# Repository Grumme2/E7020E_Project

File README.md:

# E7020E_Project

## Project Description

Our project purpose is to see whether a person is inside a perimeter or not. If the person is outside, a lamp on the board will light up.
This is going to be done with a MURATA board and a gps. We also have to implement a way to see the battery level. With the LoRa we are going to transmit the battery level, and if a user exits the perimeter, we are sending that users location.

## Higher grade

The group is aming for a higher grade than a basic pass. We are going to try to implement a charger of Lipo batteries, so that a user can charge a battery. 

## Components
* GPS: 410-237 - PmodGPS, Module UART, Digilent
* Battery charger: MCP73831T-2ACI/OT
* Battery: PIS-1218 - PiJuice Zero LiPo Battery, 500mAh, Pi Supply

https://docs.google.com/document/d/1sqJ3TY8bH1azIesI4otk2LLjVwCMFet3OU3TrjOT8jw/edit?usp=sharing

## Setup/Starting the project

### Prerequisites

In order to have the project working as intended you need to have the following things installed: 

* rustup 
* llvm-8.0
* llvm-config
* openocd
* gcc
* arm-none-eabi-gcc

### Building/running the project

First install rustup by following the instructions on https://rustup.rs/
After the installation you need to switch to the nightly toolchain rustup can use. First list the versions that are available:

`rustup toolchain list`

Then set the nightly toolchain as default:

`rustup default <nightly-toolchain>`

Then you need to install the following dependencies using rustup:

`rustup target add thumbv6m-none-eabi`

In order to start the project you first have to redirect to the **project_code** folder.

 `cd project_code`

 From that you need to make sure that you have a file called **stm32l0_dual_bank.cfg** in the **target** folder. If not, create a new file with that name that contains everything from https://github.com/ntfreak/openocd/blob/master/tcl/target/stm32l0_dual_bank.cfg

After this you may finally start **openocd**:

`openocd -f openocd.cfg`

Then open a new terminal window and redirect to the **project_code** directory, and from that you may run the program: 

`cargo run`

Now you should have a fully functional GPS-tracker on your hands!

## Team
* Anton Grahn - antgra-6@student.ltu.se
* Tom Hammarkvist - tomham-3@student.ltu.se
* Rickard Holmberg - richol-6@student.ltu.se

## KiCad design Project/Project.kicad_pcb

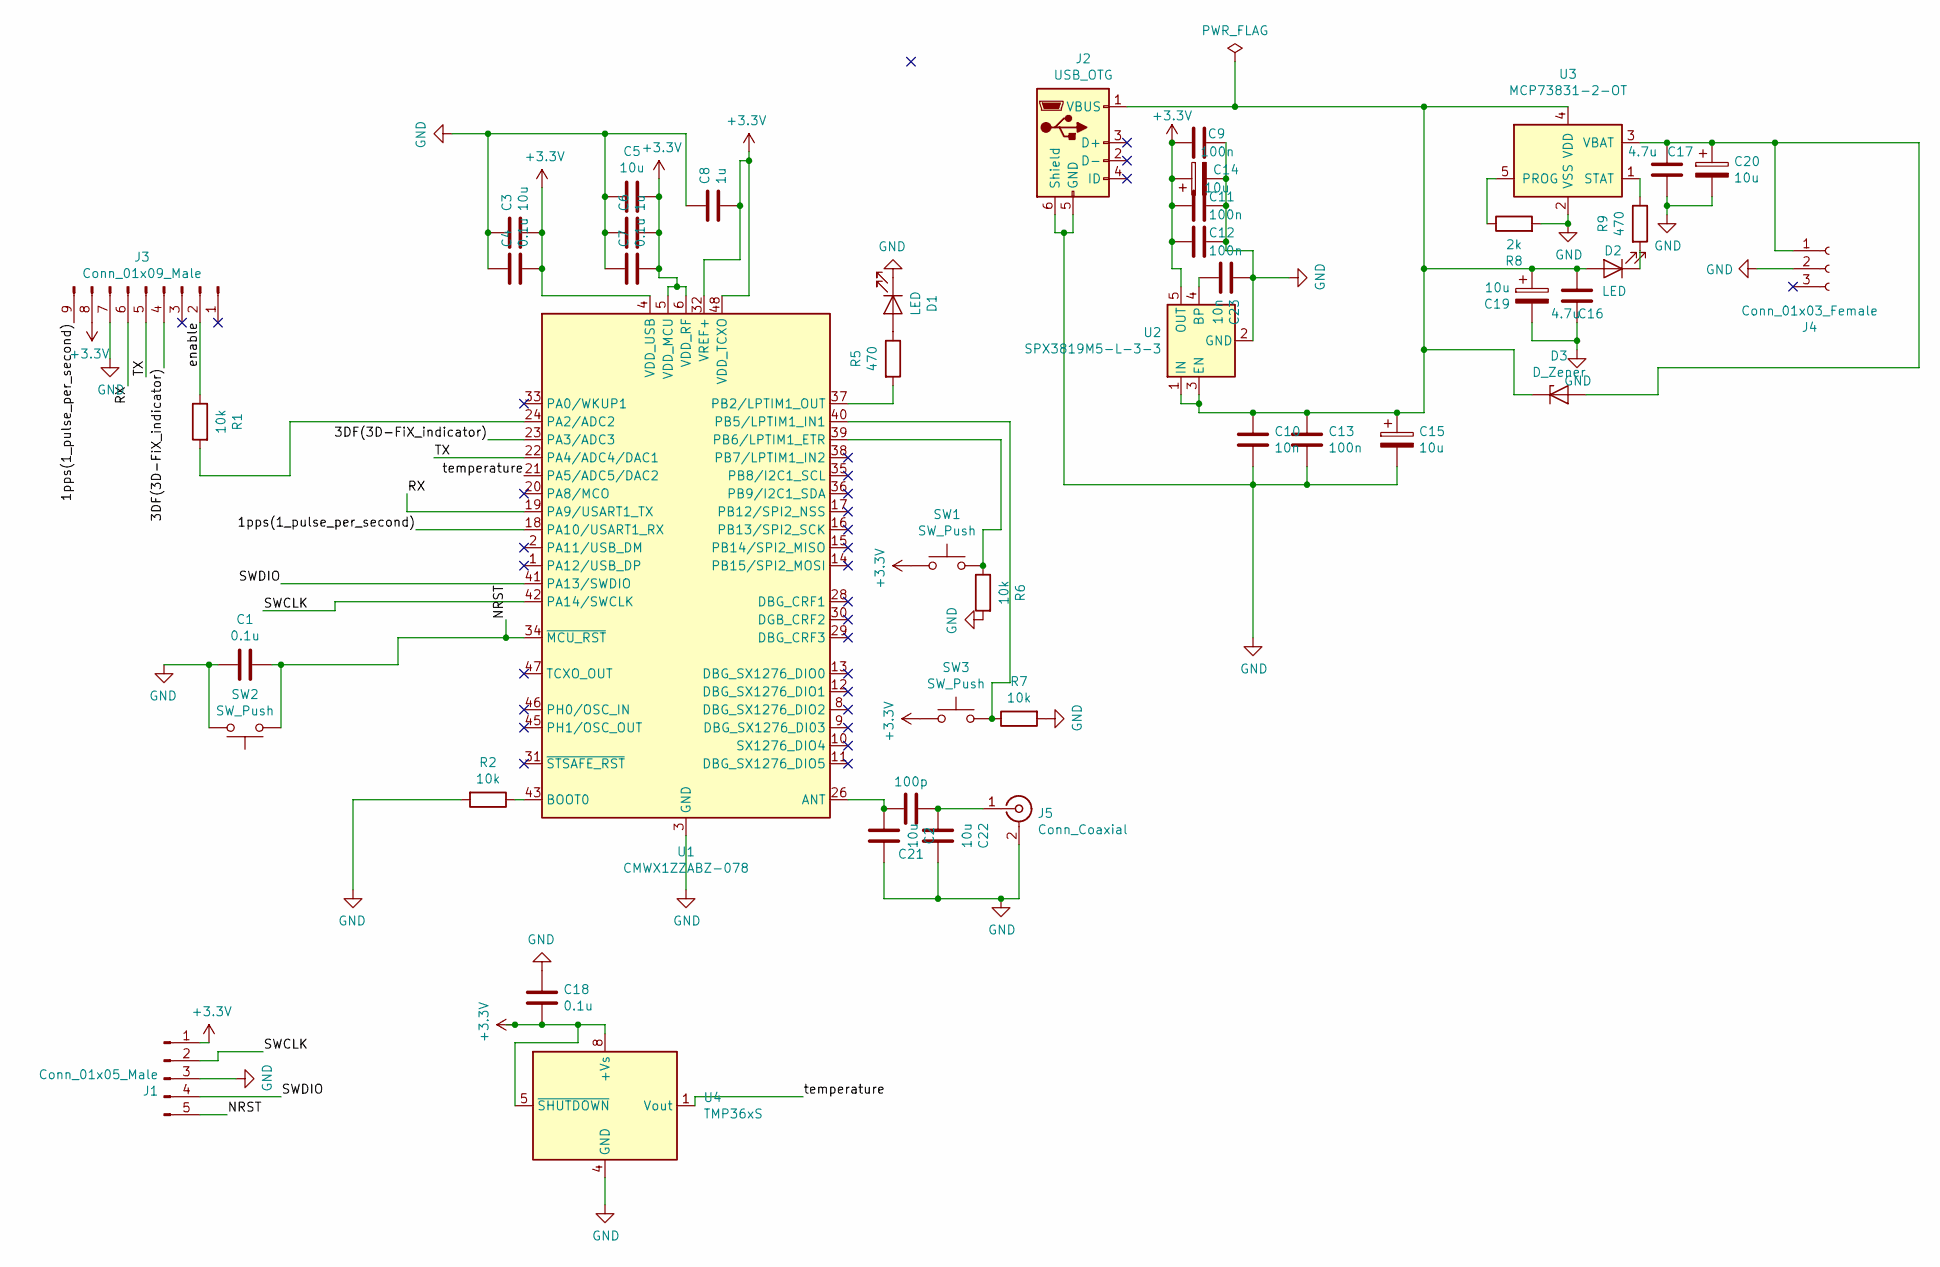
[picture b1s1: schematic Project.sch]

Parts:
C1, C4, C7, C18: 0.1u; C_0805_2012Metric_Pad1.15x1.40mm_HandSolder
C2, C3, C5, C22: 10u; C_0805_2012Metric_Pad1.15x1.40mm_HandSolder
C6, C8: 1u; C_0805_2012Metric_Pad1.15x1.40mm_HandSolder
C9, C11, C12, C13: 100n; C_0805_2012Metric_Pad1.15x1.40mm_HandSolder
C10, C23: 10n; C_0805_2012Metric_Pad1.15x1.40mm_HandSolder
C14, C15, C19, C20: 10u; CP_Elec_6.3x4.9
C16, C17: 4.7u; C_0805_2012Metric_Pad1.15x1.40mm_HandSolder
C21: 100p; C_0805_2012Metric_Pad1.15x1.40mm_HandSolder
D1, D2: LED; LED_0805_2012Metric_Pad1.15x1.40mm_HandSolder
D3: D_Zener; D_SMA_Handsoldering
J1: Conn_01x05_Male; PinHeader_1x05_P2.54mm_Vertical
J2: USB_OTG; USB_Micro-B_Wuerth_629105150521
J3: Conn_01x09_Male; PinHeader_1x09_P2.54mm_Vertical
J4: Conn_01x03_Female; JST_PH_B3B-PH-K_1x03_P2.00mm_Vertical
J5: Conn_Coaxial; U.FL_Molex_MCRF_73412-0110_Vertical
R1, R2, R6, R7: 10k; R_0805_2012Metric_Pad1.15x1.40mm_HandSolder
R5, R9: 470; R_0805_2012Metric_Pad1.15x1.40mm_HandSolder
R8: 2k; R_0805_2012Metric_Pad1.15x1.40mm_HandSolder
SW1, SW2, SW3: SW_Push; SW_Push_1P1T_NO_6x6mm_H9.5mm
U1: CMWX1ZZABZ-078; CMWX1ZZABZ_longer_pads
U2: SPX3819M5-L-3-3; SOT-23-5
U3: MCP73831-2-OT; SOT-23-5
U4: TMP36xS; SOIC-8_3.9x4.9mm_P1.27mm

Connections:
+3V3: C3.2, C4.2, C5.1, C6.2, C7.2, C8.2, C9.1, C11.2, C12.2, C14.1, C18.2, J1.1, J3.8, SW1.1, SW3.1, U1.4 (VDD_USB), U1.5 (VDD_MCU), U1.6 (VDD_RF), U1.32 (VREF+), U1.48 (VDD_TCXO), U2.5 (OUT), U4.5 (~SHUTDOWN), U4.8 (+Vs)
/1pps(1_pulse_per_second): J3.9, U1.18 (PA10/USART1_RX)
/3DF(3D-FiX_indicator): J3.4, U1.23 (PA3/ADC3)
/NRST: C1.1, J1.5, SW2.1, U1.34 (~MCU_RST)
/RX: J3.6, U1.19 (PA9/USART1_TX)
/SWCLK: J1.2, U1.42 (PA14/SWCLK)
/SWDIO: J1.4, U1.41 (PA13/SWDIO)
/TX: J3.5, U1.22 (PA4/ADC4/DAC1)
/VbAt: J3.3
/enable: J3.2, R1.1
/temperature: U1.21 (PA5/ADC5/DAC2), U4.1 (Vout)
GND: C1.2, C2.1, C3.1, C4.1, C5.2, C6.1, C7.1, C8.1, C9.2, C10.2, C11.1, C12.1, C13.2, C14.2, C15.2, C16.2, C17.1, C18.1, C19.2, C20.2, C22.1, C23.1, D1.1 (K), J1.3, J2.5 (GND), J2.6 (Shield), J3.7, J4.2, J5.2 (Ext), R2.2, R6.2, R7.2, R8.2, SW2.2, U1.3 (GND), U1.7 (GND), U1.25 (GND), U1.27 (GND), U1.44 (GND), U1.49 (GND), U1.50 (GND), U1.51 (GND), U1.52 (GND), U1.53 (GND), U1.54 (GND), U1.55 (GND), U1.56 (GND), U1.57 (GND), U2.2 (GND), U3.2 (VSS), U4.4 (GND)
unnamed: C2.2, C21.1, U1.26 (ANT)
unnamed: C10.1, C13.1, C15.1, C16.1, C19.1, D2.2 (A), D3.1 (K), J2.1 (VBUS), U2.1 (IN), U2.3 (EN), U3.4 (VDD)
unnamed: C17.2, C20.1, D3.2 (A), J4.1, U3.3 (VBAT)
unnamed: C21.2, C22.2, J5.1 (In)
unnamed: C23.2, U2.4 (BP)
unnamed: D1.2 (A), R5.1
unnamed: D2.1 (K), R9.2
unnamed: R1.2, U1.24 (PA2/ADC2)
unnamed: R2.1, U1.43 (BOOT0)
unnamed: R5.2, U1.37 (PB2/LPTIM1_OUT)
unnamed: R6.1, SW1.2, U1.39 (PB6/LPTIM1_ETR)
unnamed: R7.1, SW3.2, U1.40 (PB5/LPTIM1_IN1)
unnamed: R8.1, U3.5 (PROG)
unnamed: R9.1, U3.1 (STAT)

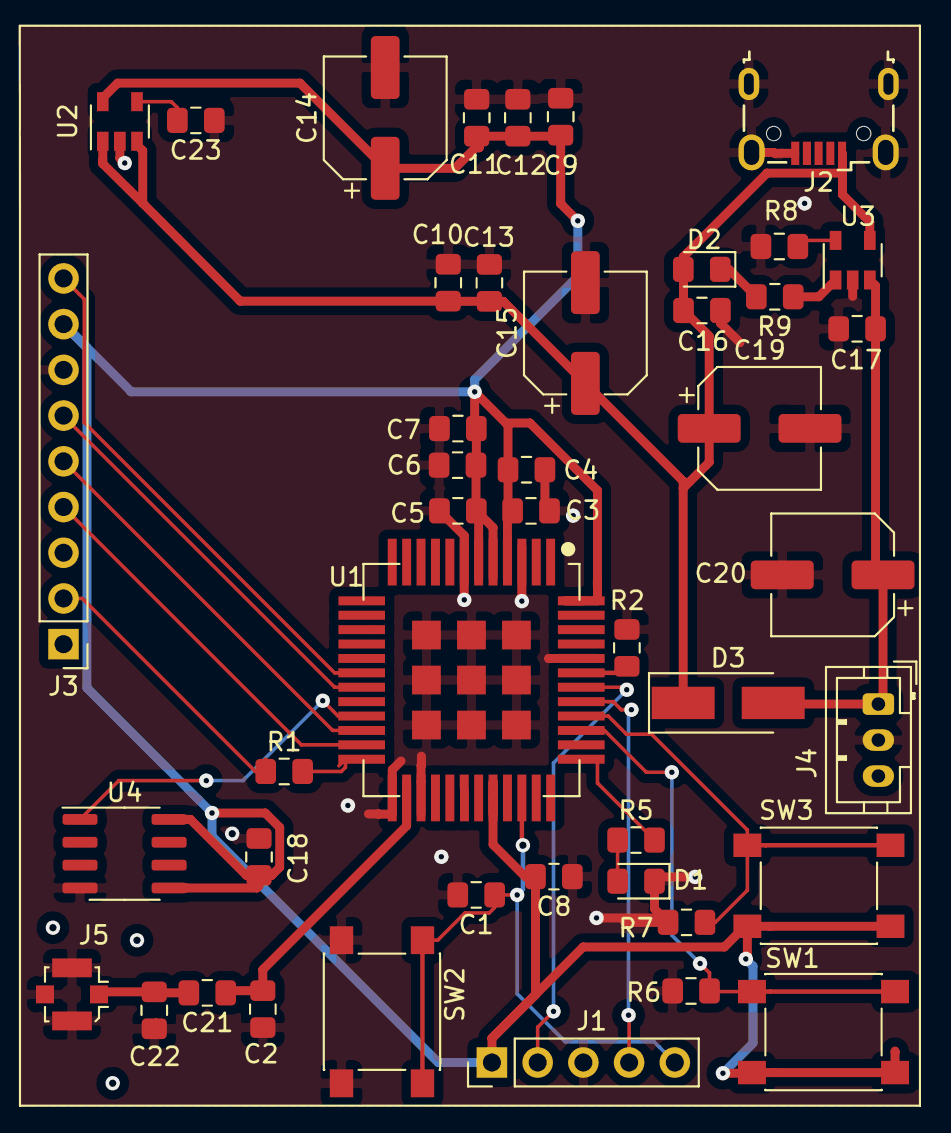
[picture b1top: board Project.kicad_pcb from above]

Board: 2 copper layers, 45 parts (0 on the bottom side), 25 nets.

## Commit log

2020-01-27 second commit
2020-01-31 Update README.md
    changed readme
2020-01-31 Update README.md
    fixed README
2020-02-05 some components added
2020-02-05 placed some more components
2020-02-06 Conn added for battery and some connections
2020-02-07 some more components and footprints
2020-02-07 more components and footprints
2020-02-10 almost all footprints and schematic done
2020-02-10 some placements put
2020-02-10 placed all components
2020-02-10 started routing
2020-02-11 some more routing
2020-02-11 all routes done and copperlayer
2020-02-11 changed some fottprints that where wrong
2020-02-12 updated schematic
2020-02-12 final design??
2020-02-13 final design probably
2020-02-13 gerber
2020-02-13 gerberfiles done
2020-02-13 done
2020-02-14 final design
2020-03-09 Added example that runs on mcu
2020-03-11 garbage that doesnt work
2020-03-11 test
2020-03-12 Button now working with LED
2020-03-12 semi working
2020-03-12 not even semi working
2020-03-12 can turn on and off led
2020-03-31 serial comunications test
2020-03-31 cont with serial, rx and tx should be correct ports
2020-04-01 gets wierd data from gps
2020-04-01 trying to get data from gps
2020-04-02 FUCKING PIECE OF SHIT WORKSgit add -Agit add -Agit add -Agit add -A
2020-04-03 some tests pending
2020-04-03 change folder name
2020-04-03 Updated read.me
